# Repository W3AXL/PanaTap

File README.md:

# PanaTap
Updated G4HUP panadapter tap

Simple revision to the G4HUP high-impedance IF tap with specific components and updated filters.

History

12/14/2017
 - Revised parts.md to add quantity of parts needed.

12/10/2017
 - Up and running on a Yaesu FT-991A

12/10/2017
 - Revised component values to values that you can actually obtain. Added digikey parts list.

10/22/2017
 - Second revision testing complete and satisfactory. Up and running on a Yaesu FT-450D

08/30/2017
 - Schematic revised to fix capacitor placement error in original schematic. New boards sent out for fabrication and testing will be done when they get back.

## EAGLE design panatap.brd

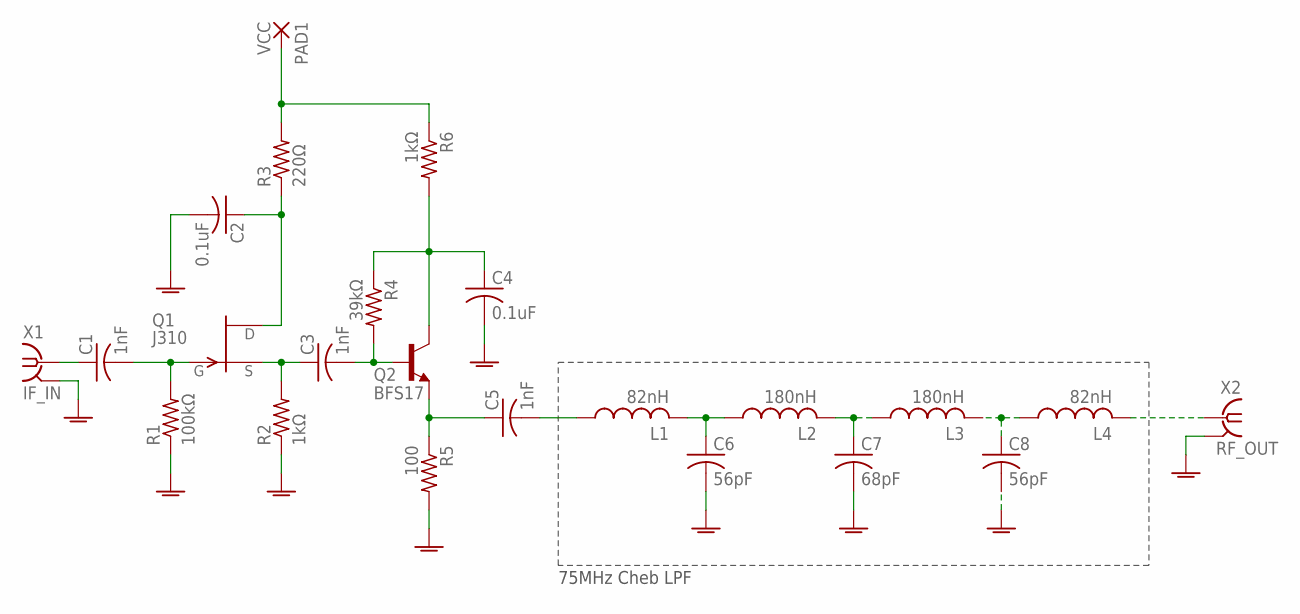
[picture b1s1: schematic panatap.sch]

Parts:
C1, C3, C5: 1nF; C1206
C2, C4: 0.1uF; C1206
C6, C8: 56pF; C1206
C7: 68pF; C1206
L1, L4: 82nH; L2012C
L2, L3: 180nH; L2012C
PAD1: VCC; SMD2,54-5,08
Q1: J310; SOT23
Q2: BFS17; SOT23
R1: 100kΩ; R1206
R2, R6: 1kΩ; R1206
R3: 220Ω; R1206
R4: 39kΩ; R1206
R5: 100; R1206
X1: IF_IN; J502-ND-142-0701-801/806
X2: RF_OUT; J502-ND-142-0701-801/806

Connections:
GNDA: C2.2, C4.2, C6.2, C7.2, C8.2, R1.1, R2.1, R5.2, X1.G@1 (2), X1.G@2 (2), X1.G@3 (2), X1.G@4 (2), X2.G@1 (2), X2.G@2 (2), X2.G@3 (2), X2.G@4 (2)
unnamed: C5.1, Q2.2 (E), R5.1
unnamed: C5.2, L1.1
unnamed: C6.1, L1.2, L2.1
unnamed: C3.2, Q2.1 (B), R4.2
unnamed: C3.1, Q1.2 (S), R2.2
unnamed: C1.2, Q1.3 (G), R1.2
unnamed: C1.1, X1.1
unnamed: PAD1.1, R3.2, R6.1
unnamed: C2.1, Q1.1 (D), R3.1
unnamed: C4.1, Q2.3 (C), R4.1, R6.2
unnamed: C7.1, L2.2, L3.1
unnamed: L4.2, X2.1
unnamed: C8.1, L3.2, L4.1

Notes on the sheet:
75MHz Cheb LPF

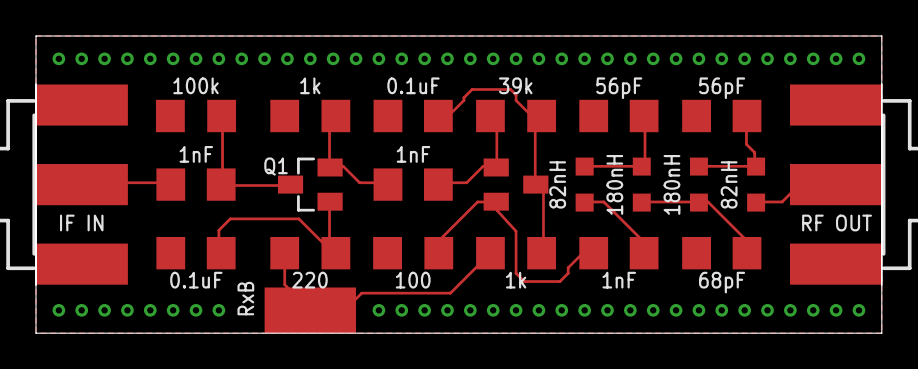
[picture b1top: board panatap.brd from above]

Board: 2 copper layers, 47.0 x 16.5 mm, 23 parts (0 on the bottom side), 14 nets.

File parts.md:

Digikey Parts List for Panatap

| Part | Digikey Part no |
| --- | --- |
| CAP 0.1uF | 399-1249-1-ND |
| CAP 0.1nF | 399-8131-1-ND |
| CAP 68pF | 399-1204-1-ND |
| CAP 56pF | 399-1203-1-ND |
| RES 100k | 	541-100KECT-ND |
| RES 100 | 	541-100ECT-ND |
| RES 39K | 	541-39KECT-ND |
| RES 220| 541-220ECT-ND |
| RES 1k | 541-1.0KECT-ND |
| JFET J310 | MMBFJ310CT-ND |
| RF NPN BFS17 | BFS17PE6327HTSA1CT-ND |
| IND 82nH | 	445-1034-1-ND |
| IND 180nH | 	445-8986-1-ND |

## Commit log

2017-08-31 Updated schematic and board with revised capacitor placement
2017-12-10 filter values changed, LTSpice added
    filter values changed to real, obtainable components and added LTSpice simulation file
2017-12-14 revise parts.md to include quantity
